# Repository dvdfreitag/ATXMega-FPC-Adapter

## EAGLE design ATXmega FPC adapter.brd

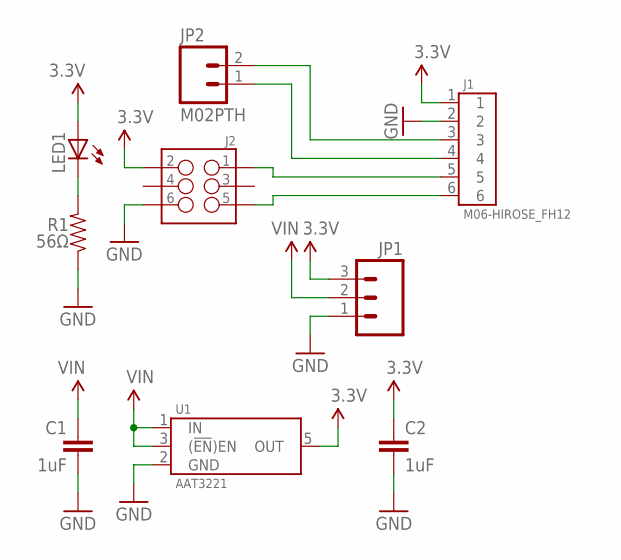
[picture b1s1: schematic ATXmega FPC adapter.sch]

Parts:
C1, C2: 1uF; 0603-CAP
J1: M06-HIROSE_FH12; FH12-6S-1SH(55)
J2: M03X2SHROUD; 2X3-SHROUDED
JP1: M03PTH; 1X03
JP2: M02PTH; 1X02
LED1: LED0603; LED-0603
R1: 56Ω; 0603-RES
U1: AAT3221; SOT23-5

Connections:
3.3V: C2.1, J1.1, J2.2, JP1.3, LED1.A, U1.5 (OUT)
GND: C1.2, C2.2, J1.2, J2.6, JP1.1, R1.1, U1.2 (GND)
unnamed: J1.5, J2.1
unnamed: J1.6, J2.5
unnamed: LED1.C, R1.2
unnamed: J1.3, JP2.2
unnamed: J1.4, JP2.1
VIN: C1.1, JP1.2, U1.1 (IN), U1.3 ((!EN!)EN)

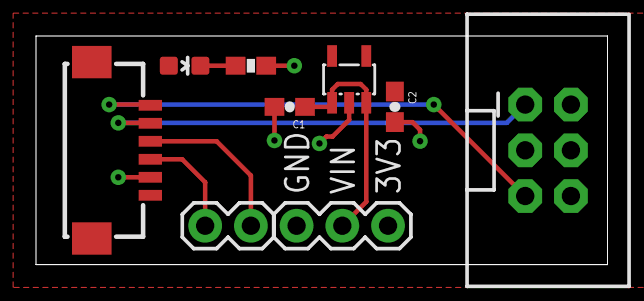
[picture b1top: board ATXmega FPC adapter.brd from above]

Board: 2 copper layers, 31.8 x 12.7 mm, 9 parts (0 on the bottom side), 8 nets.

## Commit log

2016-08-11 Create LICENSE

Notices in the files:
parts and their libraries:
SparkFun-Connectors: Licensing: Creative Commons ShareAlike 4.0 International - https://creativecommons.org/licenses/by-sa/4.0
